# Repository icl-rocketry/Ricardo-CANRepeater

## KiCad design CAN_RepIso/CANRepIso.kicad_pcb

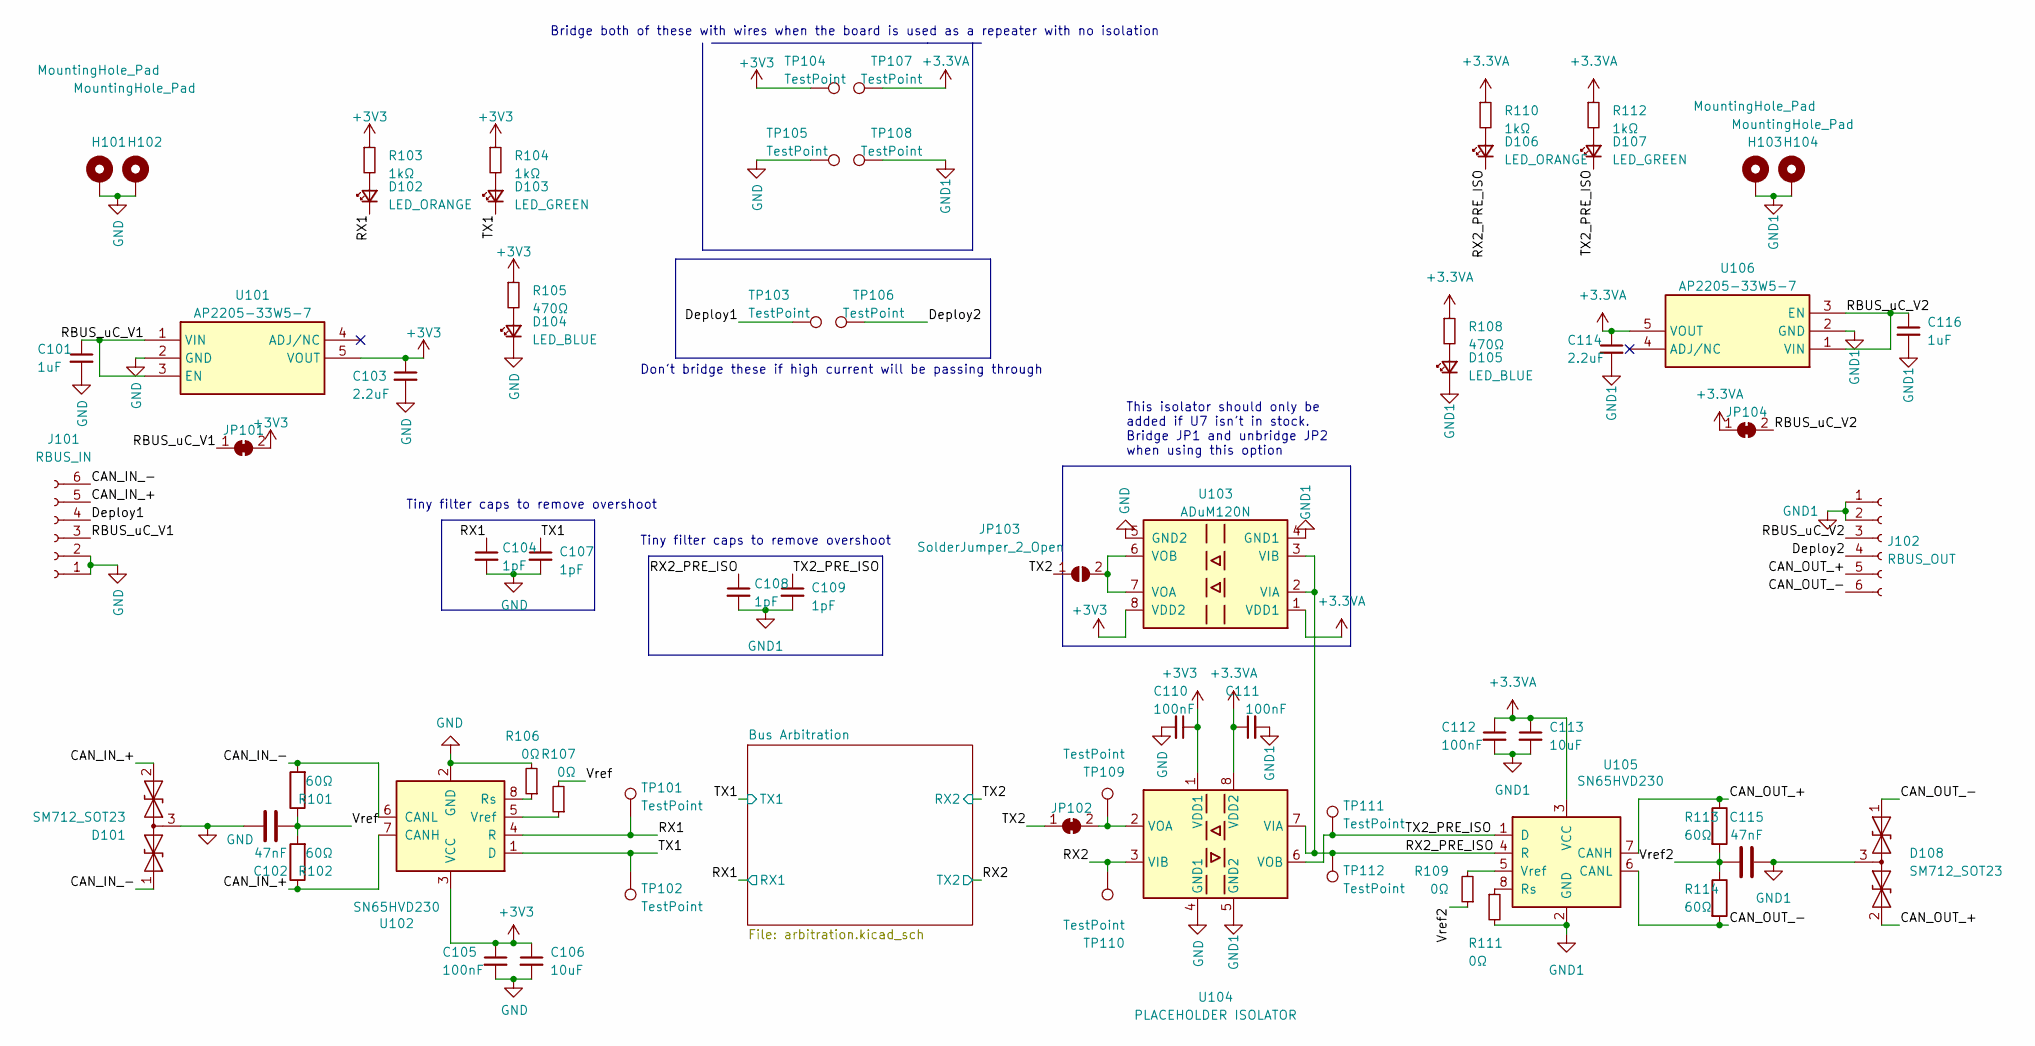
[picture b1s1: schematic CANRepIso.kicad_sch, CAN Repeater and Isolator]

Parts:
C101, C116: 1uF; C_0402_1005Metric
C102, C115: 47nF; C_0402_1005Metric
C103, C114: 2.2uF; C_0402_1005Metric
C104, C107, C108, C109: 1pF; C_0402_1005Metric
C105, C110, C111, C112: 100nF; C_0402_1005Metric
C106, C113: 10uF; C_0402_1005Metric
D101, D108: SM712_SOT23; SOT-23
D102, D106: LED_ORANGE; LED_0402_1005Metric
D103, D107: LED_GREEN; LED_0402_1005Metric
D104, D105: LED_BLUE; LED_0402_1005Metric
H101, H102, H103, H104: MountingHole_Pad; MountingHole_3.2mm_M3_DIN965_Pad
J101: RBUS_IN; Molex_Mini-Fit_Jr_5569-06A2_2x03_P4.20mm_Horizontal
J102: RBUS_OUT; Molex_Mini-Fit_Jr_5569-06A2_2x03_P4.20mm_Horizontal
JP101, JP102, JP104: SolderJumper_2_Bridged; SolderJumper-2_P1.3mm_Bridged_RoundedPad1.0x1.5mm
JP103: SolderJumper_2_Open; SolderJumper-2_P1.3mm_Open_RoundedPad1.0x1.5mm
R101, R102, R113, R114: 60Ω; R_0603_1608Metric
R103, R104, R110, R112: 1kΩ; R_0402_1005Metric
R105, R108: 470Ω; R_0402_1005Metric
R106, R111: 0Ω; R_0603_1608Metric
R107, R109: 0Ω; R_0402_1005Metric
TP101, TP102, TP109, TP110, TP111, TP112: TestPoint; TestPoint_Pad_D1.0mm
TP103, TP104, TP105, TP106, TP107, TP108: TestPoint; PinHeader_1x01_P2.54mm_Vertical
U101, U106: AP2205-33W5-7; SOT95P282X145-5N; Mouser Part Number 621-AP2205-W5-7
U102, U105: SN65HVD230; SOIC-8_3.9x4.9mm_P1.27mm
U103: ADuM120N; SOIC-8_3.9x4.9mm_P1.27mm
U104: PLACEHOLDER ISOLATOR; SOIC-8_3.9x4.9mm_P1.27mm

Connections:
+3.3VA: C111.1, C112.1, C113.1, C114.1, JP104.1 (A), R108.1, R110.1, R112.1, TP107.1, U103.1 (VDD1), U104.8 (VDD2), U105.3 (VCC), U106.5 (VOUT)
+3V3: C103.1, C105.1, C106.1, C110.1, JP101.2 (B), R103.1, R104.1, R105.1, TP104.1, U101.5 (VOUT), U102.3 (VCC), U103.8 (VDD2), U104.1 (VDD1); also elsewhere on the board
/CAN_IN_+: D101.2 (A2), J101.5, R102.1, U102.7 (CANH)
/CAN_IN_-: D101.1 (A1), J101.6, R101.2, U102.6 (CANL)
/CAN_OUT_+: D108.2 (A2), J102.5, R113.1, U105.7 (CANH)
/CAN_OUT_-: D108.1 (A1), J102.6, R114.2, U105.6 (CANL)
/Deploy1: J101.4, TP103.1
/Deploy2: J102.4, TP106.1
/RBUS_uC_V1: C101.1, J101.3, JP101.1 (A), U101.1 (VIN), U101.3 (EN)
/RBUS_uC_V2: C116.1, J102.3, JP104.2 (B), U106.1 (VIN), U106.3 (EN)
/RX1: C104.1, D102.1 (K), TP101.1, U102.4 (R); also elsewhere on the board
/RX2: TP110.1, U104.3 (VIB); also elsewhere on the board
/RX2_PRE_ISO: C108.1, D106.1 (K), TP112.1, U103.2 (VIA), U103.3 (VIB), U104.7 (VIA), U105.4 (R)
/TX1: C107.1, D103.1 (K), TP102.1, U102.1 (D); also elsewhere on the board
/TX2: JP102.1 (A), JP103.1 (A); also elsewhere on the board
/TX2_PRE_ISO: C109.1, D107.1 (K), TP111.1, U104.6 (VOB), U105.1 (D)
/Vref: C102.1, R101.1, R102.2, R107.2
/Vref2: C115.1, R109.1, R113.2, R114.1
GND: C101.2, C102.2, C103.2, C104.2, C105.2, C106.2, C107.2, C110.2, D101.3 (common), D104.1 (K), H101.1, H102.1, J101.1, J101.2, R106.2, TP105.1, U101.2 (GND), U102.2 (GND), U103.5 (GND2), U104.4 (GND1); also elsewhere on the board
GND1: C108.2, C109.2, C111.2, C112.2, C113.2, C114.2, C115.2, C116.2, D105.1 (K), D108.3 (common), H103.1, H104.1, J102.1, J102.2, R111.2, TP108.1, U103.4 (GND1), U104.5 (GND2), U105.2 (GND), U106.2 (GND)
unnamed: D102.2 (A), R103.2
unnamed: D103.2 (A), R104.2
unnamed: D104.2 (A), R105.2
unnamed: D105.2 (A), R108.2
unnamed: D106.2 (A), R110.2
unnamed: D107.2 (A), R112.2
unnamed: JP102.2 (B), TP109.1, U104.2 (VOA)
unnamed: JP103.2 (B), U103.6 (VOB), U103.7 (VOA)
unnamed: R106.1, U102.8 (Rs)
unnamed: R107.1, U102.5 (Vref)
unnamed: R111.1, U105.8 (Rs)
unnamed: R109.2, U105.5 (Vref)

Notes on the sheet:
Tiny filter caps to remove overshoot
This isolator should only be added if U7 isn't in stock. Bridge JP1 and unbridge JP2 when using this option
Don't bridge these if high current will be passing through
Bridge both of these with wires when the board is used as a repeater with no isolation

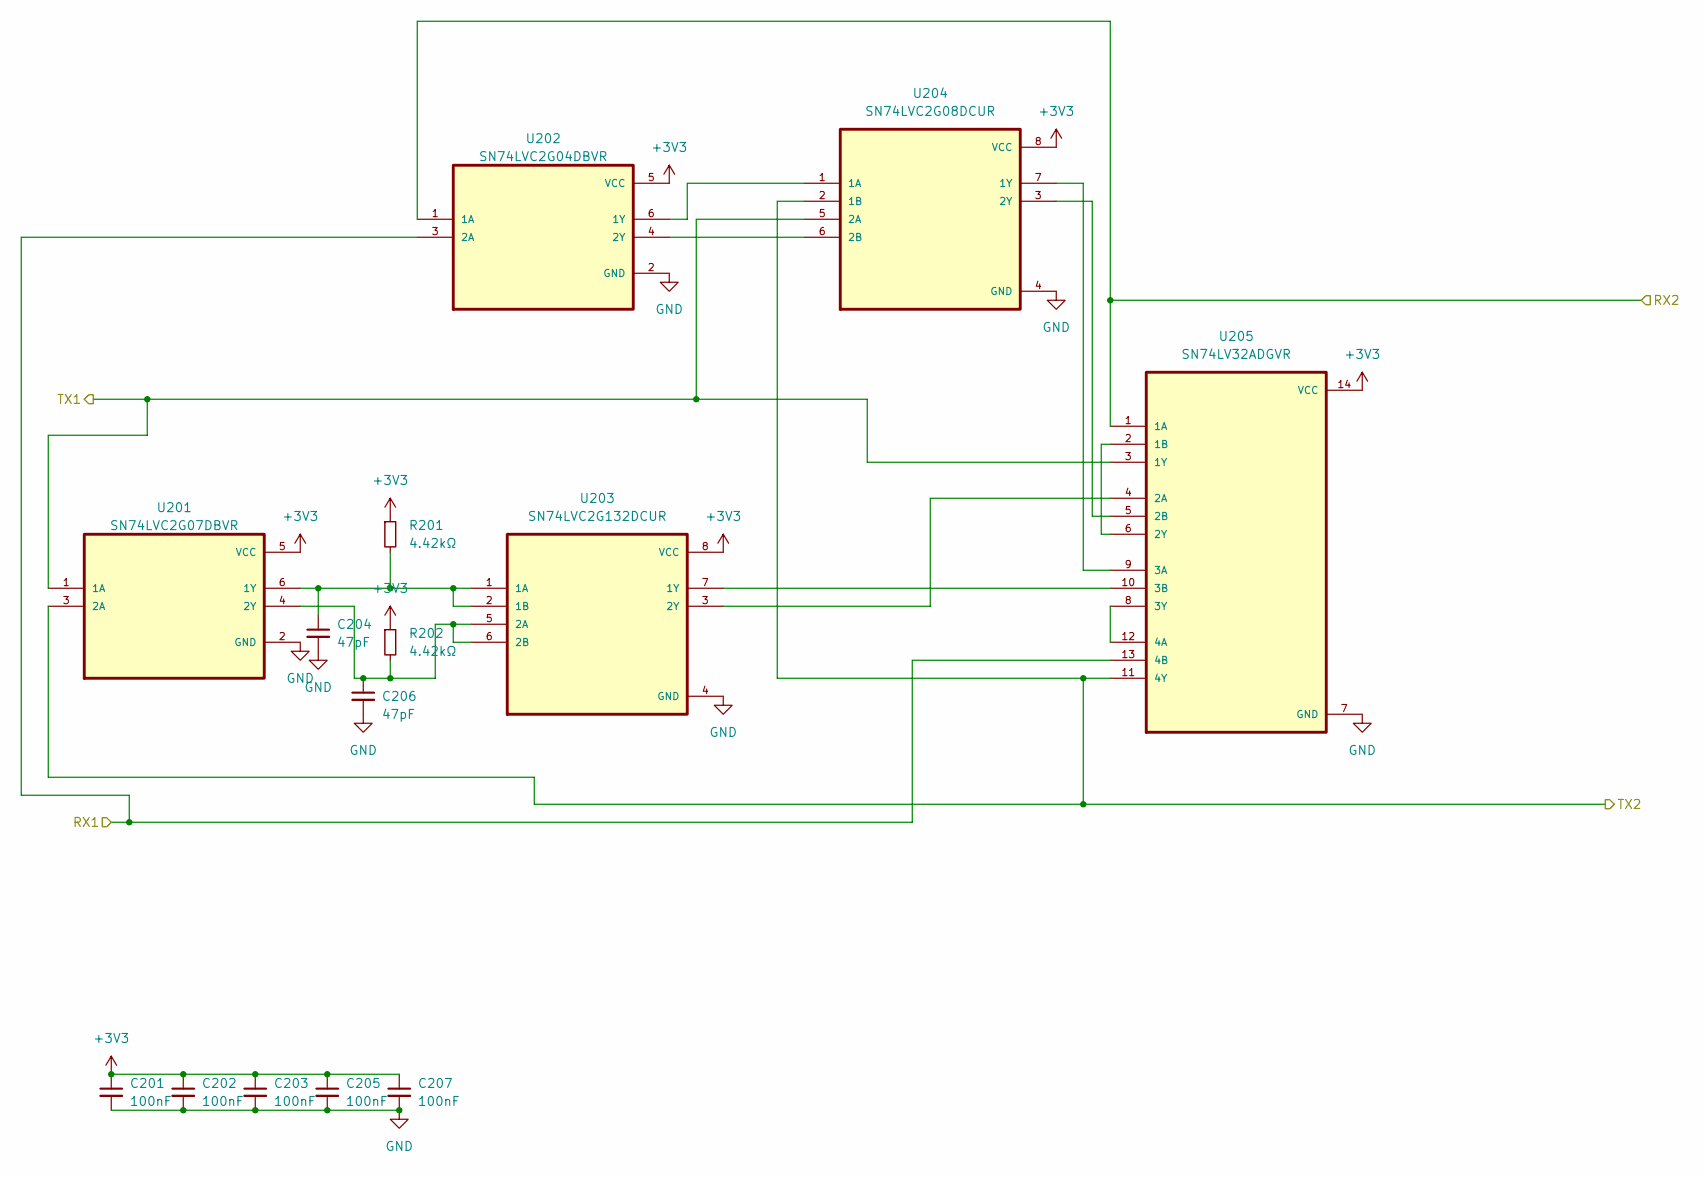
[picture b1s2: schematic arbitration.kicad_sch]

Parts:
C201, C202, C203, C205, C207: 100nF; C_0402_1005Metric
C204, C206: 47pF; C_0402_1005Metric
R201, R202: 4.42kΩ; R_0402_1005Metric
U201: SN74LVC2G07DBVR; SOT95P280X145-6N
U202: SN74LVC2G04DBVR; SOT95P280X145-6N
U203: SN74LVC2G132DCUR; SOP50P310X90-8N
U204: SN74LVC2G08DCUR; SOP50P310X90-8N
U205: SN74LV32ADGVR; SOP40P640X120-14N

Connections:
+3V3: C201.1, C202.1, C203.1, C205.1, C207.1, R201.1, R202.1, U201.5 (VCC), U202.5 (VCC), U203.8 (VCC), U204.8 (VCC), U205.14 (VCC); also elsewhere on the board
/RX1: U202.3 (2A), U205.13 (4B); also elsewhere on the board
/RX2: U201.3 (2A), U204.2 (1B), U205.11 (4Y); also elsewhere on the board
/TX1: U201.1 (1A), U204.5 (2A), U205.3 (1Y); also elsewhere on the board
/TX2: U202.1 (1A), U205.1 (1A); also elsewhere on the board
GND: C201.2, C202.2, C203.2, C204.2, C205.2, C206.2, C207.2, U201.2 (GND), U202.2 (GND), U203.4 (GND), U204.4 (GND), U205.7 (GND); also elsewhere on the board
unnamed: C204.1, R201.2, U201.6 (1Y), U203.1 (1A), U203.2 (1B)
unnamed: C206.1, R202.2, U201.4 (2Y), U203.5 (2A), U203.6 (2B)
unnamed: U202.6 (1Y), U204.1 (1A)
unnamed: U202.4 (2Y), U204.6 (2B)
unnamed: U203.7 (1Y), U205.10 (3B)
unnamed: U203.3 (2Y), U205.4 (2A)
unnamed: U204.7 (1Y), U205.9 (3A)
unnamed: U204.3 (2Y), U205.5 (2B)
unnamed: U205.2 (1B), U205.6 (2Y)
unnamed: U205.8 (3Y), U205.12 (4A)

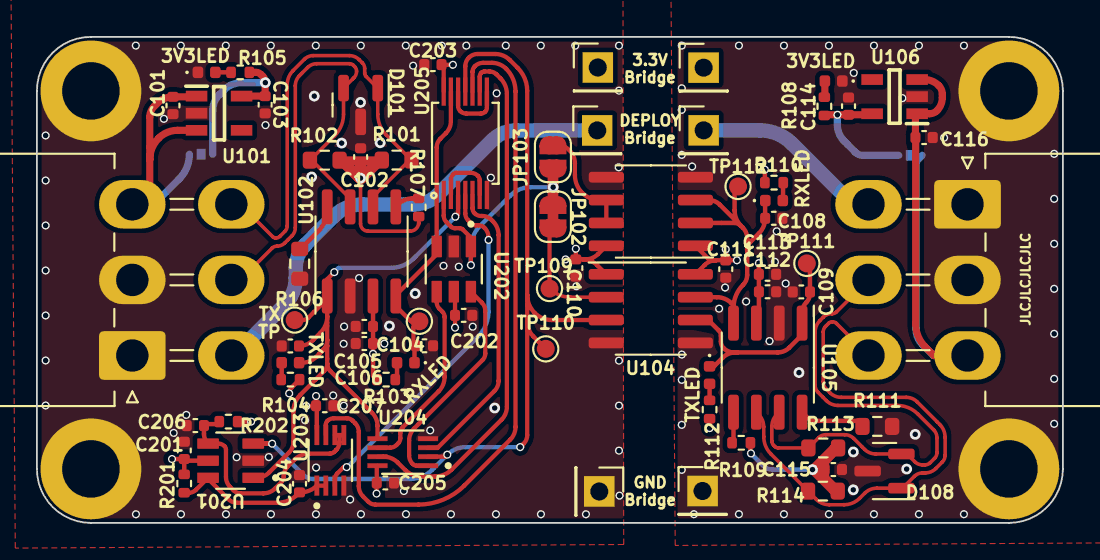
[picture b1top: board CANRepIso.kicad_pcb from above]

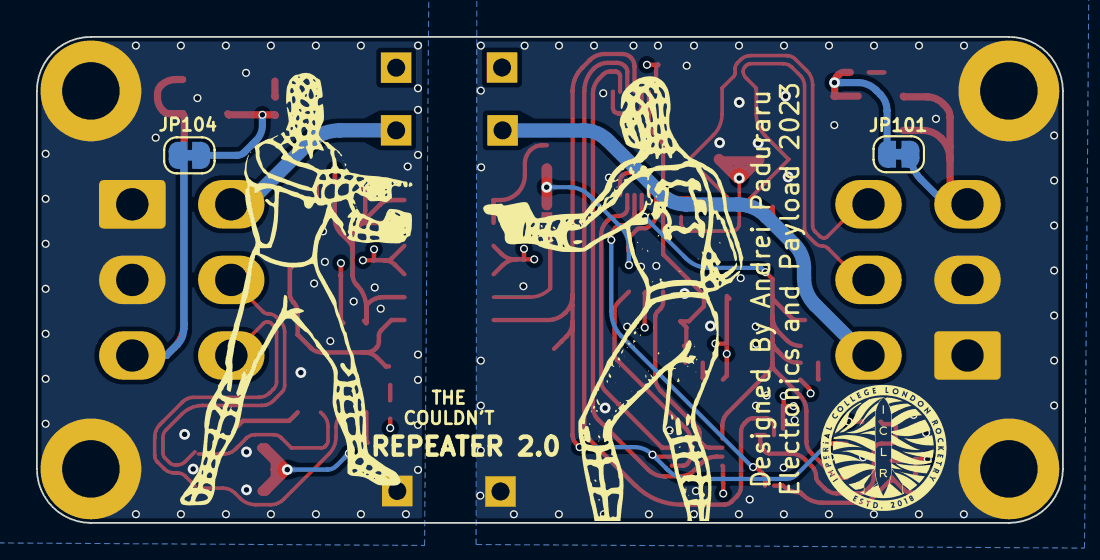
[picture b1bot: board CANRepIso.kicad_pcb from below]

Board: 4 copper layers, 57.0 x 27.0 mm, 80 parts (2 on the bottom side), 42 nets.

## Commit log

2021-12-04 Revert "Jiawei yao 2022 patch 1"
2022-04-01 Added finished schematic for CAN repeater & isolator
2022-04-04 Layout done
    still needs touchups on the planes and the rounded corner
2022-04-04 Rounded corners + via stitching
2022-04-15 changed U4 from driver to NOT gate, implemented review feedback
2022-04-15 Added text and logos
2022-05-12 added option for a 2nd digital isolator
2023-02-18 fixed schematic, layout needs update
2023-03-31 v2 finished pre-review
2023-03-31 moved literally 1 reference
2023-03-31 Fixed a stray via, removed holes from rbus connectors
2023-04-14 silkscreen tweaks
2023-06-29 some DRC
2023-07-12 oops forgot a connection
2023-07-12 some overlapping references oopsie
2024-09-12 Added 3d Components
2026-06-24 clean up schematic and bom
2026-06-24 continued
